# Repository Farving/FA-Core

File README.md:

# FA-Core
Farving Acoustics Core module

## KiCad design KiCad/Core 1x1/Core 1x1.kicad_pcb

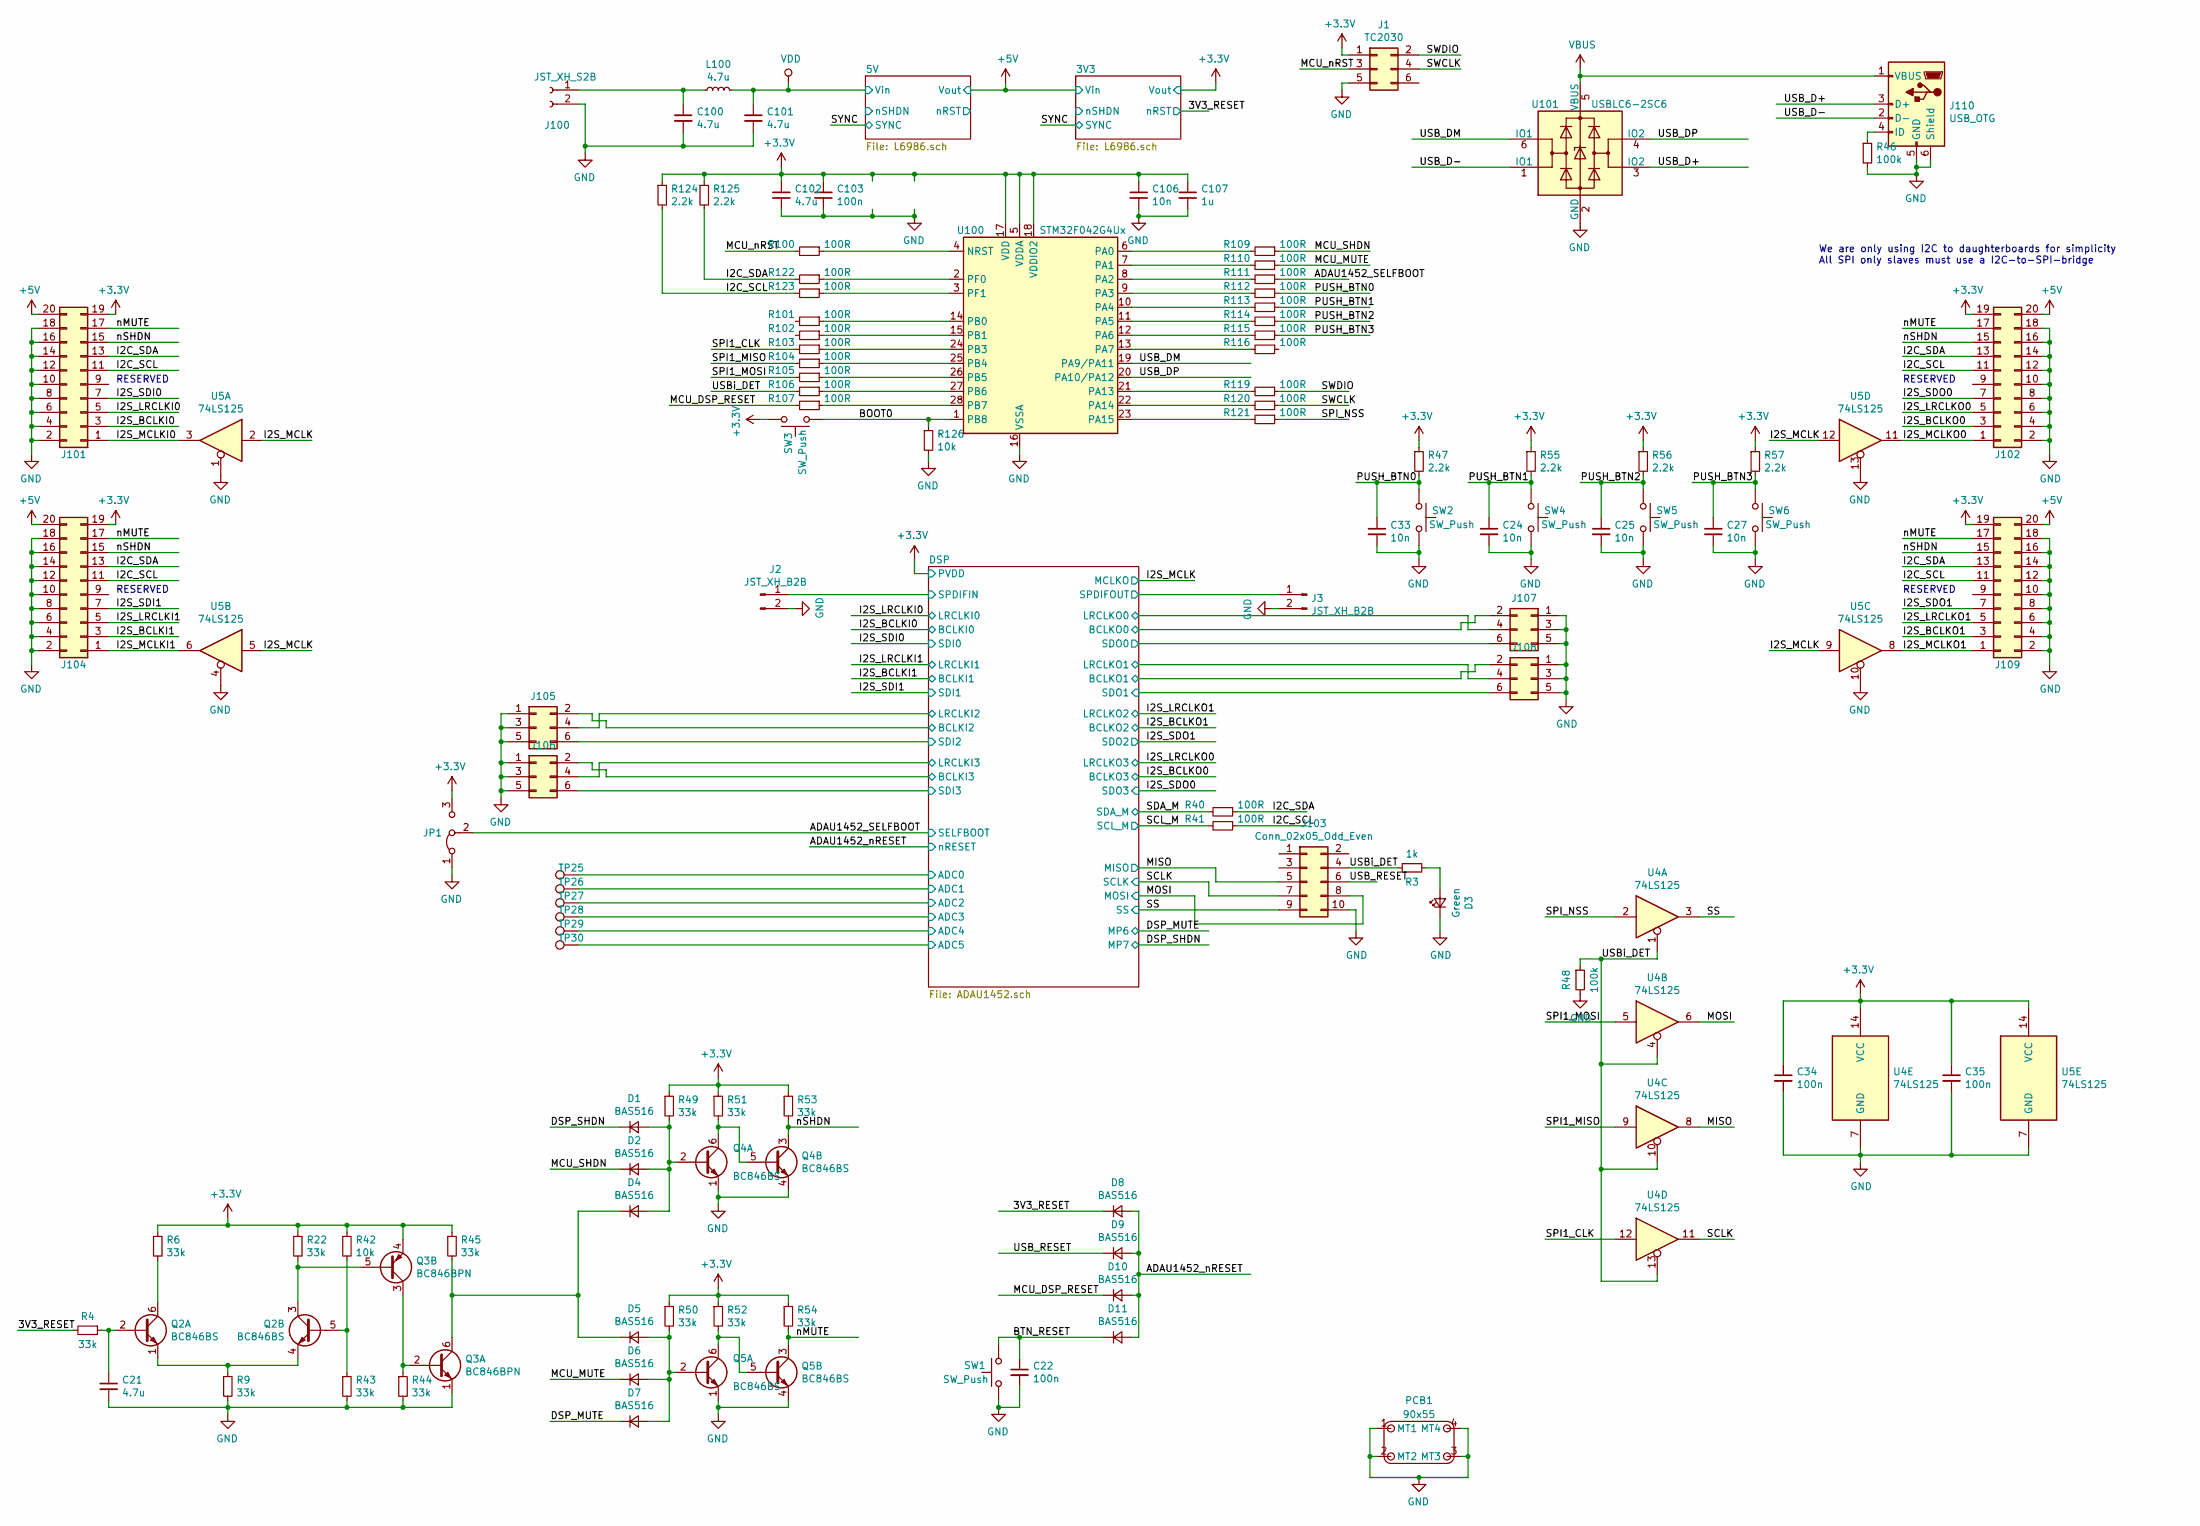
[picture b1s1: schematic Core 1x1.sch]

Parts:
C21, C102: 4.7u; C_0402_1005Metric
C22, C34, C35, C103: 100n; C_0402_1005Metric
C24, C25, C27, C33, C106: 10n; C_0402_1005Metric
C100, C101: 4.7u; C_0805_2012Metric
C107: 1u; C_0402_1005Metric
D1, D2, D4, D5, D6, D7, D8, D9, D10, D11: BAS516; D_SOD-523
D3: Green; D_0603_1608Metric
J1: TC2030; Tag-Connect_TC2030-IDC-NL_2x03_P1.27mm_Vertical
J2, J3: JST_XH_B2B; JST_XH_B2B-XH-A_1x02_P2.50mm_Vertical
J100: JST_XH_S2B; JST_XH_S2B-XH-A_1x02_P2.50mm_Horizontal
J101, J102: 02x10; PinHeader_2x10_P2.54mm_Horizontal
J103: Conn_02x05_Odd_Even; PinHeader_2x05_P2.54mm_Vertical
J104, J109: 02x10; PinHeader_2x10_P2.54mm_Vertical
J105, J106, J107, J108: Conn_02x03_Odd_Even; PinHeader_2x03_P2.54mm_Vertical
J110: USB_OTG; USB_Micro-B_Molex-105017-0001
JP1: Jumper_3_Bridged12; PinHeader_1x03_P2.54mm_Vertical
L100: 4.7u; L_Pulse_PA4546.XXXNLT
PCB1: 90x55; PCB_Board_90x55
Q2, Q4, Q5: BC846BS; SOT-363_SC-70-6
Q3: BC846BPN; SOT-363_SC-70-6
R3: 1k; R_0402_1005Metric
R4, R6, R9, R22, R43, R44, R45, R49, R50, R51, R52, R53, R54: 33k; R_0402_1005Metric
R40, R41, R100, R101, R102, R103, R104, R105, R106, R107, R109, R110, R111, R112, R113, R114, R115, R116, R119, R120, R121, R122, R123: 100R; R_0402_1005Metric
R42, R126: 10k; R_0402_1005Metric
R46, R48: 100k; R_0402_1005Metric
R47, R55, R56, R57, R124, R125: 2.2k; R_0402_1005Metric
SW1, SW2, SW3, SW4, SW5, SW6: SW_Push; SW_SPST_PTS810
TP25, TP26, TP27, TP28, TP29, TP30: TestPoint; TestPoint_Pad_D1.0mm
U4, U5: 74LS125; TSSOP-14_4.4x5mm_P0.65mm
U100: STM32F042G4Ux; QFN-28_4x4mm_P0.5mm
U101: USBLC6-2SC6; SOT-23-6

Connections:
+3V3: C34.1, C35.1, C102.1, C103.1, C106.1, C107.1, J1.1, J101.19, J102.19, J104.19, J109.19, JP1.3 (B), Q3.4 (E2), R6.1, R22.1, R42.1, R45.1, R47.1, R49.1, R50.1, R51.1, R52.1, R53.1, R54.1, R55.1, R56.1, R57.1, R124.1, R125.1, SW3.2, U4.14 (VCC), U5.14 (VCC), U100.5 (VDDA), U100.17 (VDD), U100.18 (VDDIO2); also elsewhere on the board
+5V: J101.20, J102.20, J104.20, J109.20; also elsewhere on the board
/3V3_RESET: D8.1 (K), R4.2; also elsewhere on the board
/ADAU1452_SELFBOOT: JP1.2 (C), R111.1; also elsewhere on the board
/ADAU1452_nRESET: D8.2 (A), D9.2 (A), D10.2 (A), D11.2 (A); also elsewhere on the board
/BOOT0: R126.1, SW3.1, U100.1 (PB8)
/BTN_RESET: C22.1, D11.1 (K), SW1.2
/DSP/ADC0: TP25.1; also elsewhere on the board
/DSP/ADC1: TP26.1; also elsewhere on the board
/DSP/ADC2: TP27.1; also elsewhere on the board
/DSP/ADC3: TP28.1; also elsewhere on the board
/DSP/ADC4: TP29.1; also elsewhere on the board
/DSP/ADC5: TP30.1; also elsewhere on the board
/DSP/BCLKI2: J105.2; also elsewhere on the board
/DSP/BCLKI3: J106.2; also elsewhere on the board
/DSP/BCLKO0: J107.2; also elsewhere on the board
/DSP/BCLKO1: J108.2; also elsewhere on the board
/DSP/LRCLKI2: J105.4; also elsewhere on the board
/DSP/LRCLKI3: J106.4; also elsewhere on the board
/DSP/LRCLKO0: J107.4; also elsewhere on the board
/DSP/LRCLKO1: J108.4; also elsewhere on the board
/DSP/SDI2: J105.6; also elsewhere on the board
/DSP/SDI3: J106.6; also elsewhere on the board
/DSP/SDO0: J107.6; also elsewhere on the board
/DSP/SDO1: J108.6; also elsewhere on the board
/DSP/SPDIFIN: J2.1; also elsewhere on the board
/DSP/SPDIFOUT: J3.1; also elsewhere on the board
/DSP_MUTE: D7.1 (K); also elsewhere on the board
/DSP_SHDN: D1.1 (K); also elsewhere on the board
/I2C_SCL: J101.11, J102.11, J104.11, J109.11, R41.1, R123.2, R124.2
/I2C_SDA: J101.13, J102.13, J104.13, J109.13, R40.1, R122.2, R125.2
/I2S_BCLKI0: J101.3; also elsewhere on the board
/I2S_BCLKI1: J104.3; also elsewhere on the board
/I2S_BCLKO0: J102.3; also elsewhere on the board
/I2S_BCLKO1: J109.3; also elsewhere on the board
/I2S_LRCLKI0: J101.5; also elsewhere on the board
/I2S_LRCLKI1: J104.5; also elsewhere on the board
/I2S_LRCLKO0: J102.5; also elsewhere on the board
/I2S_LRCLKO1: J109.5; also elsewhere on the board
/I2S_MCLK: U5.2, U5.5, U5.9, U5.12; also elsewhere on the board
/I2S_MCLKI0: J101.1, U5.3
/I2S_MCLKI1: J104.1, U5.6
/I2S_MCLKO0: J102.1, U5.11
/I2S_MCLKO1: J109.1, U5.8
/I2S_SDI0: J101.7; also elsewhere on the board
/I2S_SDI1: J104.7; also elsewhere on the board
/I2S_SDO0: J102.7; also elsewhere on the board
/I2S_SDO1: J109.7; also elsewhere on the board
/MCU_DSP_RESET: D10.1 (K), R107.2
/MCU_MUTE: D6.1 (K), R110.1
/MCU_SHDN: D2.1 (K), R109.1
/MCU_nRST: J1.3, R100.2
/MISO: J103.5, U4.8; also elsewhere on the board
/MOSI: J103.8, U4.6; also elsewhere on the board
/PUSH_BTN0: C33.1, R47.2, R112.1, SW2.2
/PUSH_BTN1: C24.1, R55.2, R113.1, SW4.2
/PUSH_BTN2: C25.1, R56.2, R114.1, SW5.2
/PUSH_BTN3: C27.1, R57.2, R115.1, SW6.2
/SCLK: J103.7, U4.11; also elsewhere on the board
/SCL_M: R41.2; also elsewhere on the board
/SDA_M: R40.2; also elsewhere on the board
/SPI1_CLK: R103.2, U4.12
/SPI1_MISO: R104.2, U4.9
/SPI1_MOSI: R105.2, U4.5
/SPI_NSS: R121.1, U4.2
/SS: J103.9, U4.3; also elsewhere on the board
/SWCLK: J1.4, R120.1
/SWDIO: J1.2, R119.1
/USB_D+: J110.3 (D+), U101.3 (IO2)
/USB_D-: J110.2 (D-), U101.1 (IO1)
/USB_DM: U100.19 (PA9/PA11), U101.6 (IO1)
/USB_DP: U100.20 (PA10/PA12), U101.4 (IO2)
/USB_RESET: D9.1 (K), J103.6
/USBi_DET: J103.4, R3.1, R48.1, R106.2, U4.1, U4.4, U4.10, U4.13
/nMUTE: J101.17, J102.17, J104.17, J109.17, Q5.3 (C2), R54.2
/nSHDN: J101.15, J102.15, J104.15, J109.15, Q4.3 (C2), R53.2
GND: C21.2, C22.2, C24.2, C25.2, C27.2, C33.2, C34.2, C35.2, C100.2, C101.2, C102.2, C103.2, C106.2, C107.2, D3.1 (K), J1.5, J2.2, J3.2, J100.2, J101.2, J101.4, J101.6, J101.8, J101.10, J101.12, J101.14, J101.16, J101.18, J102.2, J102.4, J102.6, J102.8, J102.10, J102.12, J102.14, J102.16, J102.18, J103.10, J104.2, J104.4, J104.6, J104.8, J104.10, J104.12, J104.14, J104.16, J104.18, J105.1, J105.3, J105.5, J106.1, J106.3, J106.5, J107.1, J107.3, J107.5, J108.1, J108.3, J108.5, J109.2, J109.4, J109.6, J109.8, J109.10, J109.12, J109.14, J109.16, J109.18, J110.5 (GND), J110.6 (Shield), JP1.1 (A), PCB1.1 (MT1), PCB1.2 (MT2), PCB1.3 (MT3), PCB1.4 (MT4), Q3.1 (E1), Q4.1 (E1), Q4.4 (E2), Q5.1 (E1), Q5.4 (E2), R9.2, R43.2, R44.2, R46.2, R48.2, R126.2, SW1.1, SW2.1, SW4.1, SW5.1, SW6.1, U4.7 (GND), U5.1, U5.4, U5.7 (GND), U5.10, U5.13, U100.16 (VSSA), U101.2 (GND); also elsewhere on the board
unnamed: C21.1, Q2.2 (B1), R4.1
unnamed: C100.1, J100.1, L100.1
unnamed: D1.2 (A), D2.2 (A), D4.2 (A), Q4.2 (B1), R49.2
unnamed: D3.2 (A), R3.2
unnamed: D4.1 (K), D5.1 (K), Q3.6 (C1), R45.2
unnamed: D5.2 (A), D6.2 (A), D7.2 (A), Q5.2 (B1), R50.2
unnamed: J110.4 (ID), R46.1
unnamed: Q2.1 (E1), Q2.4 (E2), R9.1
unnamed: Q2.3 (C2), Q3.5 (B2), R22.2
unnamed: Q2.5 (B2), R42.2, R43.1
unnamed: Q2.6 (C1), R6.2
unnamed: Q3.2 (B1), Q3.3 (C2), R44.1
unnamed: Q4.5 (B2), Q4.6 (C1), R51.2
unnamed: Q5.5 (B2), Q5.6 (C1), R52.2
unnamed: R100.1, U100.4 (NRST)
unnamed: R101.1, U100.14 (PB0)
unnamed: R102.1, U100.15 (PB1)
unnamed: R103.1, U100.24 (PB3)
unnamed: R104.1, U100.25 (PB4)
unnamed: R105.1, U100.26 (PB5)
unnamed: R106.1, U100.27 (PB6)
unnamed: R107.1, U100.28 (PB7)
unnamed: R109.2, U100.6 (PA0)
unnamed: R110.2, U100.7 (PA1)
unnamed: R111.2, U100.8 (PA2)
unnamed: R112.2, U100.9 (PA3)
unnamed: R113.2, U100.10 (PA4)
unnamed: R114.2, U100.11 (PA5)
unnamed: R115.2, U100.12 (PA6)
unnamed: R116.2, U100.13 (PA7)
unnamed: R119.2, U100.21 (PA13)
unnamed: R120.2, U100.22 (PA14)
unnamed: R121.2, U100.23 (PA15)
unnamed: R122.1, U100.2 (PF0)
unnamed: R123.1, U100.3 (PF1)
VBUS: J110.1 (VBUS), U101.5 (VBUS)
VDD: C101.1, L100.2; also elsewhere on the board

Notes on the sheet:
We are only using I2C to daughterboards for simplicity All SPI only slaves must use a I2C-to-SPI-bridge
RESERVED

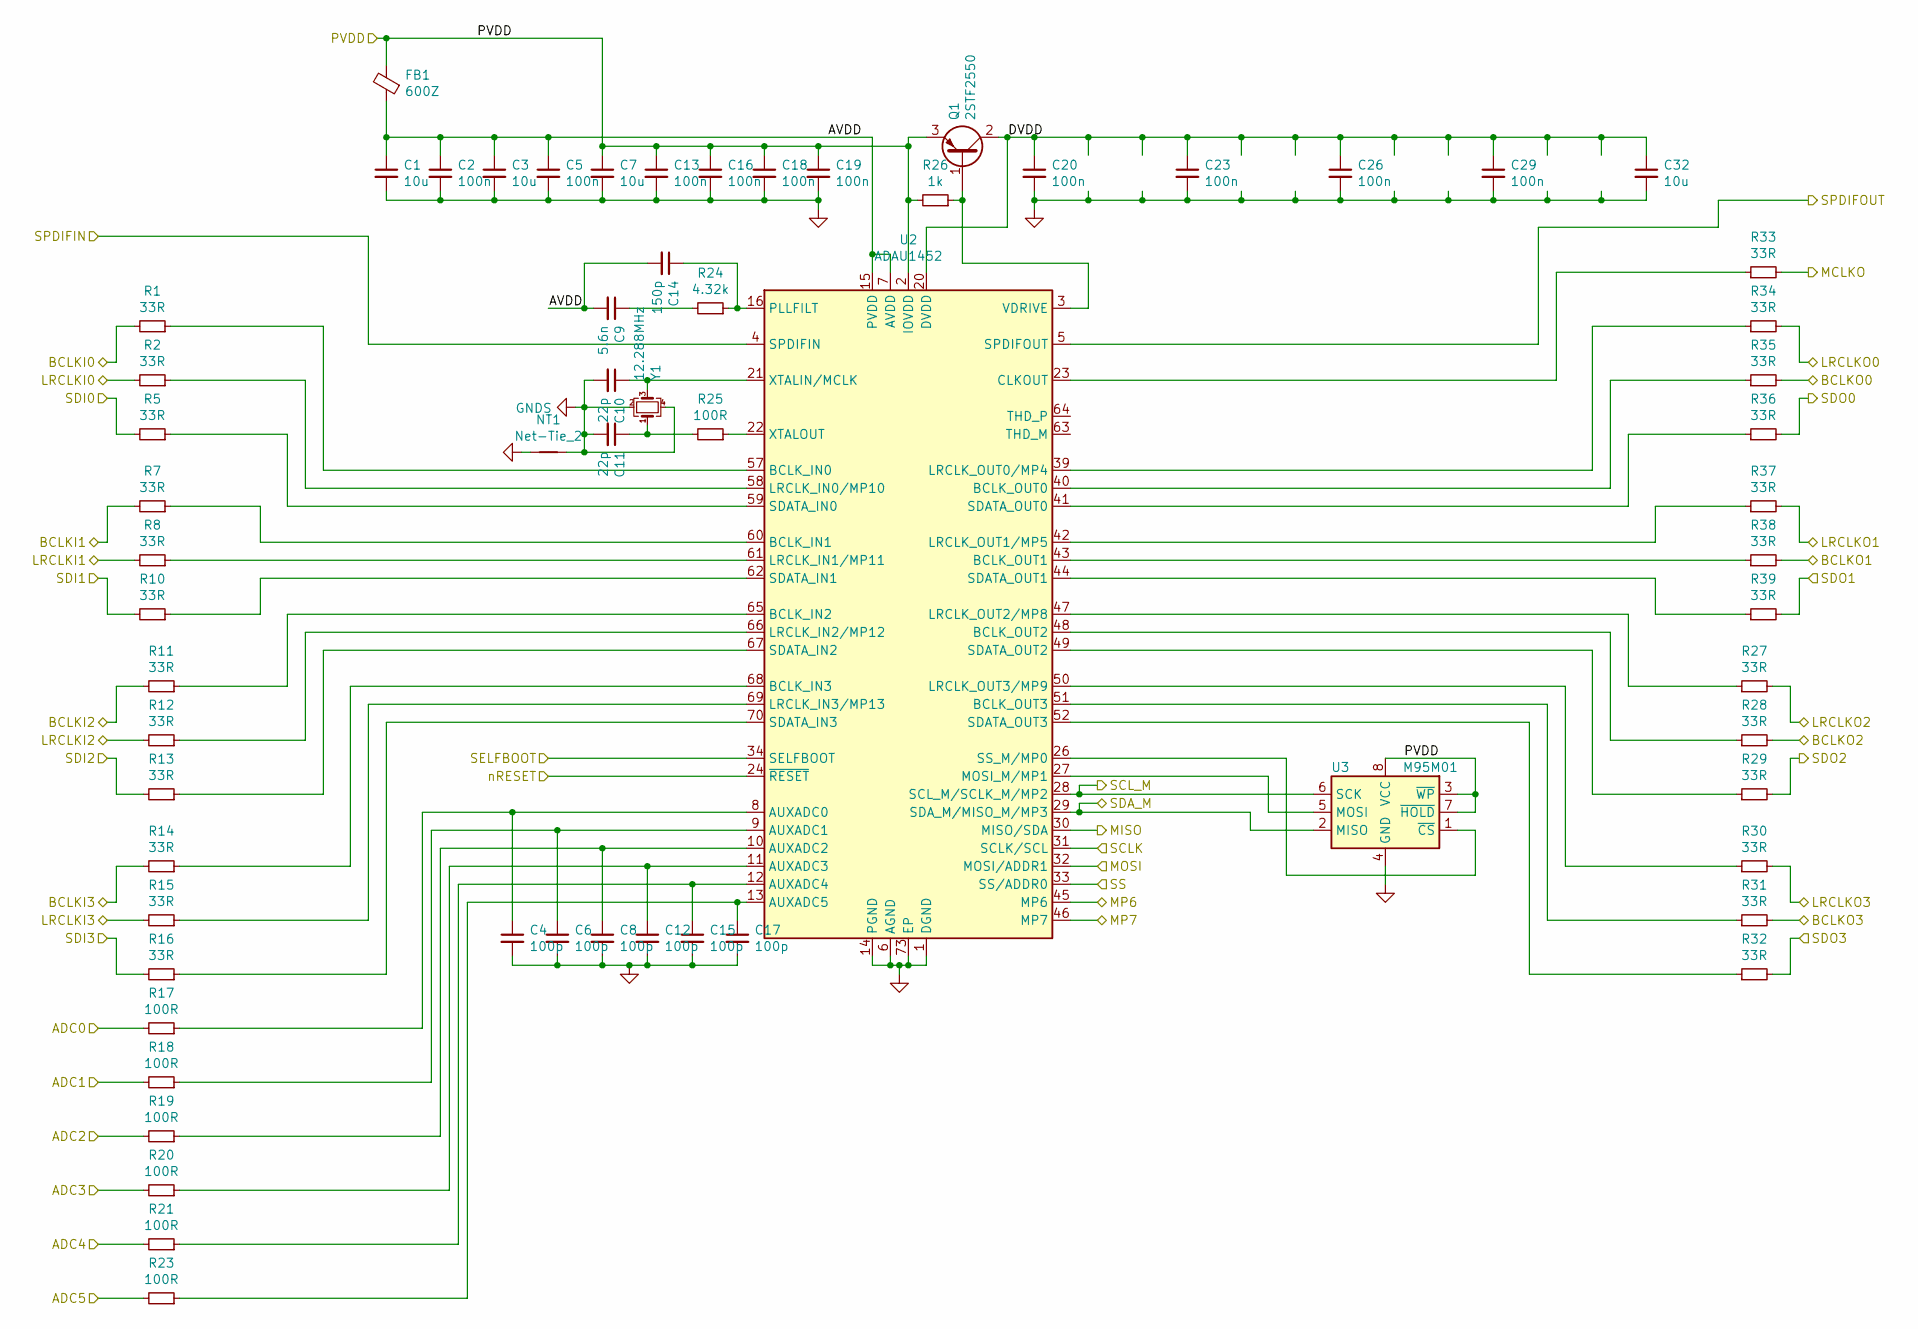
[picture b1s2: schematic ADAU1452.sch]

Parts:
C1, C3, C7, C32: 10u; C_0402_1005Metric
C2, C5, C13, C16, C18, C19, C20, C23, C26, C29: 100n; C_0402_1005Metric
C4, C6, C8, C12, C15, C17: 100p; C_0402_1005Metric
C9: 5.6n; C_0402_1005Metric
C10, C11: 22p; C_0402_1005Metric
C14: 150p; C_0402_1005Metric
FB1: 600Z; L_0402_1005Metric
NT1: Net-Tie_2; NetTie-2_SMD_Pad0.5mm
Q1: 2STF2550; SOT-89-3
R1, R2, R5, R7, R8, R10, R11, R12, R13, R14, R15, R16, R27, R28, R29, R30, R31, R32, R33, R34, R35, R36, R37, R38, R39: 33R; R_0402_1005Metric
R17, R18, R19, R20, R21, R23, R25: 100R; R_0402_1005Metric
R24: 4.32k; R_0402_1005Metric
R26: 1k; R_0402_1005Metric
U2: ADAU1452; LFCSP-72-1EP_10x10mm_P0.5mm_EP5.3x5.3mm
U3: M95M01; SO-8_3.9x4.9mm_P1.27mm
Y1: 12.288MHz; Crystal_SMD_5032-4Pin_5.0x3.2mm

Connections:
+3V3: C7.1, C13.1, C16.1, C18.1, C19.1, FB1.2, Q1.3 (E), R26.2, U2.2 (IOVDD), U2.18 (IOVDD), U2.38 (IOVDD), U2.56 (IOVDD), U3.3 (~WP), U3.7 (~HOLD), U3.8 (VCC); also elsewhere on the board
/ADAU1452_SELFBOOT: U2.34 (SELFBOOT); also elsewhere on the board
/ADAU1452_nRESET: U2.24 (~RESET); also elsewhere on the board
/DSP/ADC0: R17.2; also elsewhere on the board
/DSP/ADC1: R18.2; also elsewhere on the board
/DSP/ADC2: R19.2; also elsewhere on the board
/DSP/ADC3: R20.2; also elsewhere on the board
/DSP/ADC4: R21.2; also elsewhere on the board
/DSP/ADC5: R23.2; also elsewhere on the board
/DSP/AVDD: C1.1, C2.1, C3.1, C5.1, C9.2, C14.2, FB1.1, U2.7 (AVDD), U2.15 (PVDD)
/DSP/BCLKI2: R11.2; also elsewhere on the board
/DSP/BCLKI3: R14.2; also elsewhere on the board
/DSP/BCLKO0: R35.2; also elsewhere on the board
/DSP/BCLKO1: R38.2; also elsewhere on the board
/DSP/DVDD: C20.1, C23.1, C26.1, C29.1, C32.1, Q1.2 (C), U2.20 (DVDD), U2.35 (DVDD), U2.53 (DVDD), U2.71 (DVDD)
/DSP/LRCLKI2: R12.2; also elsewhere on the board
/DSP/LRCLKI3: R15.2; also elsewhere on the board
/DSP/LRCLKO0: R34.2; also elsewhere on the board
/DSP/LRCLKO1: R37.2; also elsewhere on the board
/DSP/SDI2: R13.2; also elsewhere on the board
/DSP/SDI3: R16.2; also elsewhere on the board
/DSP/SDO0: R36.2; also elsewhere on the board
/DSP/SDO1: R39.2; also elsewhere on the board
/DSP/SPDIFIN: U2.4 (SPDIFIN); also elsewhere on the board
/DSP/SPDIFOUT: U2.5 (SPDIFOUT); also elsewhere on the board
/DSP_MUTE: U2.45 (MP6); also elsewhere on the board
/DSP_SHDN: U2.46 (MP7); also elsewhere on the board
/I2S_BCLKI0: R1.2; also elsewhere on the board
/I2S_BCLKI1: R7.2; also elsewhere on the board
/I2S_BCLKO0: R31.2; also elsewhere on the board
/I2S_BCLKO1: R28.2; also elsewhere on the board
/I2S_LRCLKI0: R2.2; also elsewhere on the board
/I2S_LRCLKI1: R8.2; also elsewhere on the board
/I2S_LRCLKO0: R30.2; also elsewhere on the board
/I2S_LRCLKO1: R27.2; also elsewhere on the board
/I2S_MCLK: R33.2; also elsewhere on the board
/I2S_SDI0: R5.2; also elsewhere on the board
/I2S_SDI1: R10.2; also elsewhere on the board
/I2S_SDO0: R32.2; also elsewhere on the board
/I2S_SDO1: R29.2; also elsewhere on the board
/MISO: U2.30 (MISO/SDA); also elsewhere on the board
/MOSI: U2.32 (MOSI/ADDR1); also elsewhere on the board
/SCLK: U2.31 (SCLK/SCL); also elsewhere on the board
/SCL_M: U2.28 (SCL_M/SCLK_M/MP2), U3.6 (SCK); also elsewhere on the board
/SDA_M: U2.29 (SDA_M/MISO_M/MP3), U3.2 (MISO); also elsewhere on the board
/SS: U2.33 (SS/ADDR0); also elsewhere on the board
GND: C1.2, C2.2, C3.2, C4.2, C5.2, C6.2, C7.2, C8.2, C12.2, C13.2, C15.2, C16.2, C17.2, C18.2, C19.2, C20.2, C23.2, C26.2, C29.2, C32.2, NT1.1, U2.1 (DGND), U2.6 (AGND), U2.14 (PGND), U2.17 (DGND), U2.19 (DGND), U2.25 (DGND), U2.36 (DGND), U2.37 (DGND), U2.54 (DGND), U2.55 (DGND), U2.72 (DGND), U2.73 (EP), U3.4 (GND); also elsewhere on the board
GNDS: C10.2, C11.2, NT1.2, Y1.2, Y1.4
unnamed: C4.1, R17.1, U2.8 (AUXADC0)
unnamed: C6.1, R18.1, U2.9 (AUXADC1)
unnamed: C8.1, R19.1, U2.10 (AUXADC2)
unnamed: C9.1, R24.2
unnamed: C10.1, U2.21 (XTALIN/MCLK), Y1.3
unnamed: C11.1, R25.2, Y1.1
unnamed: C12.1, R20.1, U2.11 (AUXADC3)
unnamed: C14.1, R24.1, U2.16 (PLLFILT)
unnamed: C15.1, R21.1, U2.12 (AUXADC4)
unnamed: C17.1, R23.1, U2.13 (AUXADC5)
unnamed: Q1.1 (B), R26.1, U2.3 (VDRIVE)
unnamed: R1.1, U2.57 (BCLK_IN0)
unnamed: R2.1, U2.58 (LRCLK_IN0/MP10)
unnamed: R5.1, U2.59 (SDATA_IN0)
unnamed: R7.1, U2.60 (BCLK_IN1)
unnamed: R8.1, U2.61 (LRCLK_IN1/MP11)
unnamed: R10.1, U2.62 (SDATA_IN1)
unnamed: R11.1, U2.65 (BCLK_IN2)
unnamed: R12.1, U2.66 (LRCLK_IN2/MP12)
unnamed: R13.1, U2.67 (SDATA_IN2)
unnamed: R14.1, U2.68 (BCLK_IN3)
unnamed: R15.1, U2.69 (LRCLK_IN3/MP13)
unnamed: R16.1, U2.70 (SDATA_IN3)
unnamed: R25.1, U2.22 (XTALOUT)
unnamed: R27.1, U2.47 (LRCLK_OUT2/MP8)
unnamed: R28.1, U2.48 (BCLK_OUT2)
unnamed: R29.1, U2.49 (SDATA_OUT2)
unnamed: R30.1, U2.50 (LRCLK_OUT3/MP9)
unnamed: R31.1, U2.51 (BCLK_OUT3)
unnamed: R32.1, U2.52 (SDATA_OUT3)
unnamed: R33.1, U2.23 (CLKOUT)
unnamed: R34.1, U2.39 (LRCLK_OUT0/MP4)
unnamed: R35.1, U2.40 (BCLK_OUT0)
unnamed: R36.1, U2.41 (SDATA_OUT0)
unnamed: R37.1, U2.42 (LRCLK_OUT1/MP5)
unnamed: R38.1, U2.43 (BCLK_OUT1)
unnamed: R39.1, U2.44 (SDATA_OUT1)
unnamed: U2.26 (SS_M/MP0), U3.1 (~CS)
unnamed: U2.27 (MOSI_M/MP1), U3.5 (MOSI)

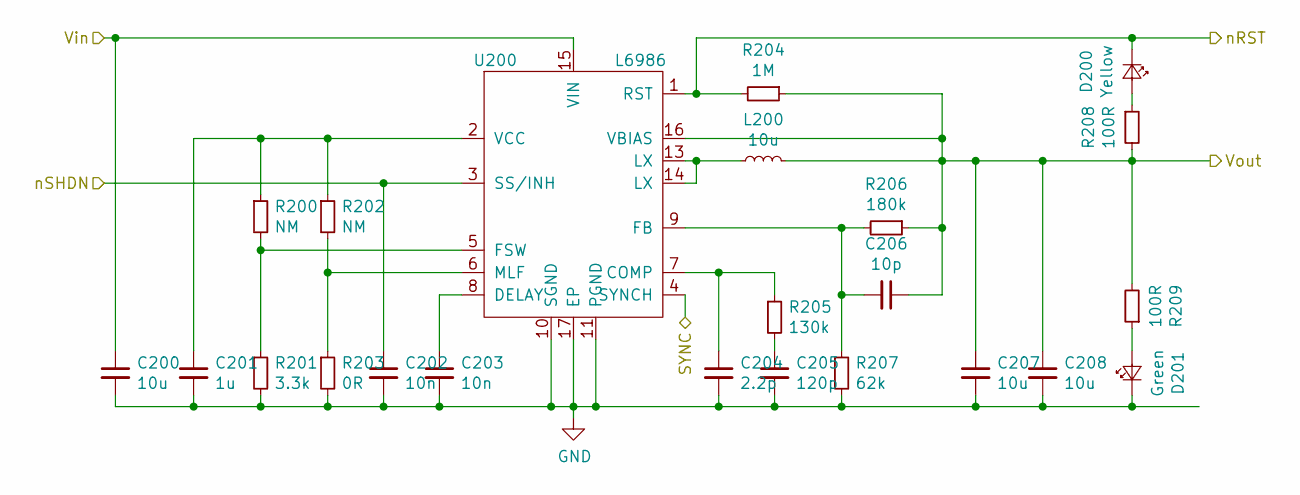
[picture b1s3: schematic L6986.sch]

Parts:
C200, C207, C208: 10u; C_0805_2012Metric
C201: 1u; C_0402_1005Metric
C202, C203: 10n; C_0402_1005Metric
C204: 2.2p; C_0402_1005Metric
C205: 120p; C_0402_1005Metric
C206: 10p; C_0402_1005Metric
D200: Yellow; D_0603_1608Metric
D201: Green; D_0603_1608Metric
L200: 10u; L_Pulse_PA4546.XXXNLT
R200, R202: NM; R_0402_1005Metric
R201: 3.3k; R_0402_1005Metric
R203: 0R; R_0402_1005Metric
R204: 1M; R_0402_1005Metric
R205: 130k; R_0402_1005Metric
R206: 180k; R_0402_1005Metric
R207: 62k; R_0402_1005Metric
R208, R209: 100R; R_0402_1005Metric
U200: L6986; HTSSOP-16-1EP_4.4x5mm_P0.65mm_EP3x3mm

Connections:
+5V: C206.1, C207.1, C208.1, L200.2, R204.1, R206.1, R208.2, R209.2, U200.16 (VBIAS); also elsewhere on the board
/5V/nRST: D200.1 (K), R204.2, U200.1 (RST)
/5V/nSHDN: C202.1, U200.3 (SS/INH)
/SYNC: U200.4 (SYNCH); also elsewhere on the board
GND: C200.2, C201.2, C202.2, C203.2, C204.2, C205.2, C207.2, C208.2, D201.1 (K), R201.2, R203.2, R207.2, U200.10 (SGND), U200.11 (PGND), U200.12 (PGND), U200.17 (EP); also elsewhere on the board
unnamed: C201.1, R200.1, R202.1, U200.2 (VCC)
unnamed: C203.1, U200.8 (DELAY)
unnamed: C204.1, R205.1, U200.7 (COMP)
unnamed: C205.1, R205.2
unnamed: C206.2, R206.2, R207.1, U200.9 (FB)
unnamed: D200.2 (A), R208.1
unnamed: D201.2 (A), R209.1
unnamed: L200.1, U200.13 (LX), U200.14 (LX)
unnamed: R200.2, R201.1, U200.5 (FSW)
unnamed: R202.2, R203.1, U200.6 (MLF)
VDD: C200.1, U200.15 (VIN); also elsewhere on the board

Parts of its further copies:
C300, C307, C308: 10u; C_0805_2012Metric
C301: 1u; C_0402_1005Metric
C302, C303: 10n; C_0402_1005Metric
C304: 2.2p; C_0402_1005Metric
C305: 120p; C_0402_1005Metric
C306: 10p; C_0402_1005Metric
D300: Yellow; D_0603_1608Metric
D301: Green; D_0603_1608Metric
L300: 10u; L_Pulse_PA4546.XXXNLT
R300, R302: NM; R_0402_1005Metric
R301: 3.3k; R_0402_1005Metric
R303: 0R; R_0402_1005Metric
R304: 1M; R_0402_1005Metric
R305: 130k; R_0402_1005Metric
R306: 180k; R_0402_1005Metric
R307: 62k; R_0402_1005Metric
R308, R309: 100R; R_0402_1005Metric
U300: L6986; HTSSOP-16-1EP_4.4x5mm_P0.65mm_EP3x3mm

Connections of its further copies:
+3V3: C306.1, C307.1, C308.1, L300.2, R304.1, R306.1, R308.2, R309.2, U300.16 (VBIAS); also elsewhere on the board
+5V: C300.1, U300.15 (VIN); also elsewhere on the board
/3V3/nSHDN: C302.1, U300.3 (SS/INH)
/3V3_RESET: D300.1 (K), R304.2, U300.1 (RST); also elsewhere on the board
/SYNC: U300.4 (SYNCH); also elsewhere on the board
GND: C300.2, C301.2, C302.2, C303.2, C304.2, C305.2, C307.2, C308.2, D301.1 (K), R301.2, R303.2, R307.2, U300.10 (SGND), U300.11 (PGND), U300.12 (PGND), U300.17 (EP); also elsewhere on the board
unnamed: C301.1, R300.1, R302.1, U300.2 (VCC)
unnamed: C303.1, U300.8 (DELAY)
unnamed: C304.1, R305.1, U300.7 (COMP)
unnamed: C305.1, R305.2
unnamed: C306.2, R306.2, R307.1, U300.9 (FB)
unnamed: D300.2 (A), R308.1
unnamed: D301.2 (A), R309.1
unnamed: L300.1, U300.13 (LX), U300.14 (LX)
unnamed: R300.2, R301.1, U300.5 (FSW)
unnamed: R302.2, R303.1, U300.6 (MLF)

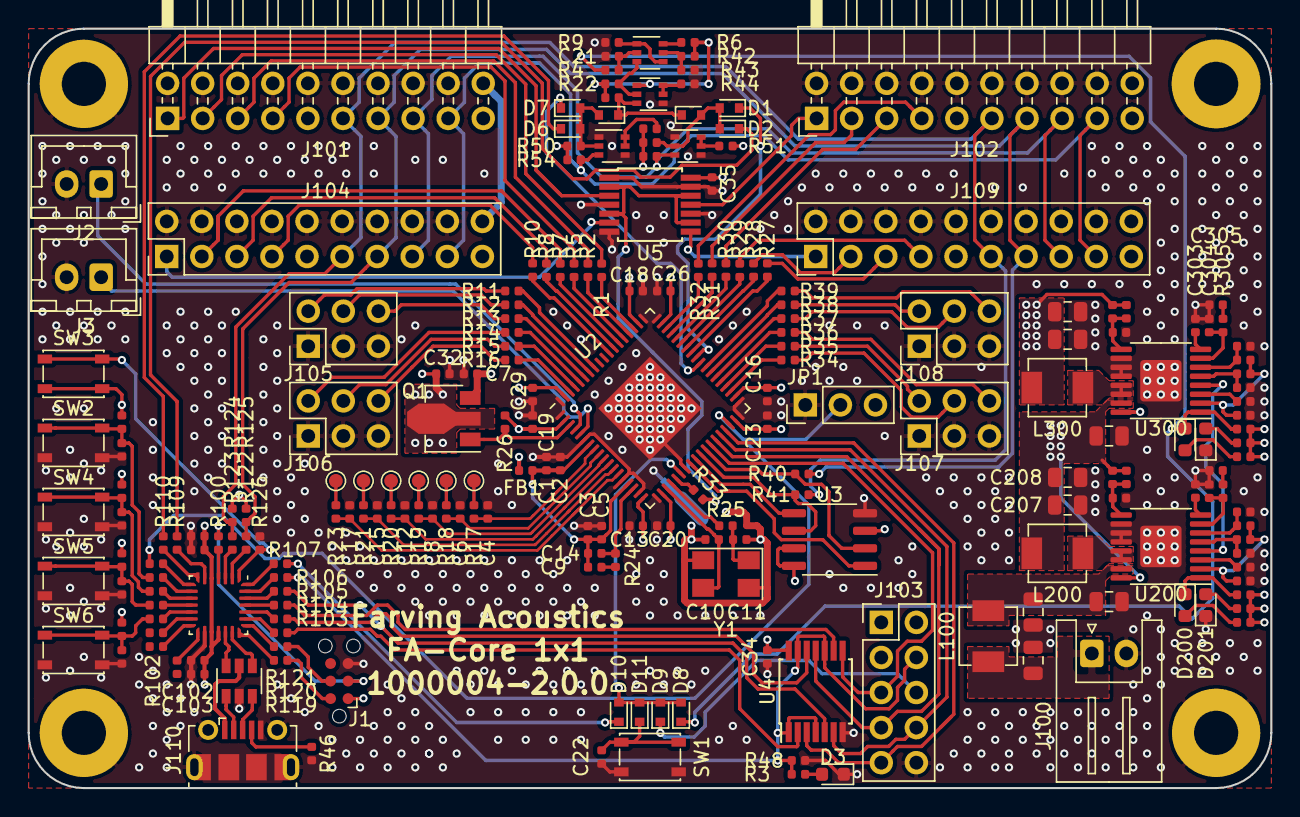
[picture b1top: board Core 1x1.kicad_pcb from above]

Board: 4 copper layers, 90.0 x 55.0 mm, 219 parts (1 on the bottom side), 180 nets.
